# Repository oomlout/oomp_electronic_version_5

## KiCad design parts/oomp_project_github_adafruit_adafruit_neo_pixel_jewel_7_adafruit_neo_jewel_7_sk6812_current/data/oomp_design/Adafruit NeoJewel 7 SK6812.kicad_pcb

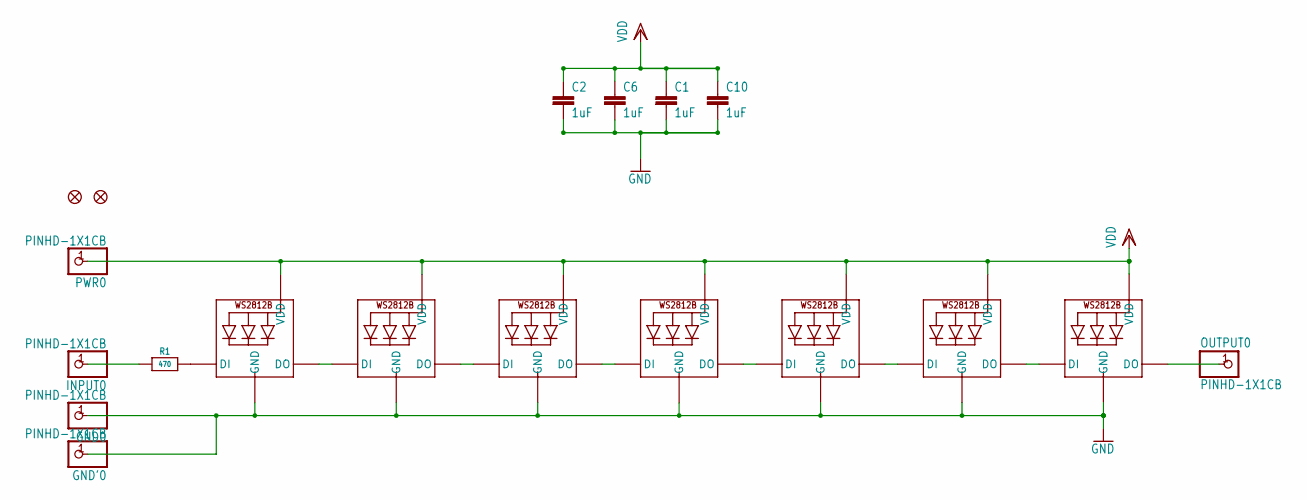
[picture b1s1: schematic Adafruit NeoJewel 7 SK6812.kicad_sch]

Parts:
C1, C2, C6, C10: 1uF; C0603
FID1, FID2: FIDUCIAL_1MM
GND0: PINHD-1X1CB; 1X01-CLEANBIG
GND'0: PINHD-1X1CB; 1X01-CLEANBIG
INPUT0: PINHD-1X1CB; 1X01-CLEANBIG
LED1, LED2, LED3, LED4, LED5, LED6, LED7: WS2812B_5050N; WS2812B-NARROW
OUTPUT0: PINHD-1X1CB; 1X01-CLEANBIG
PWR0: PINHD-1X1CB; 1X01-CLEANBIG
R1: 470; 0603-NO

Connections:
GND: C1.2, C2.2, C6.2, C10.2, GND0.1, GND'0.1, LED1.3-GND (GND), LED2.3-GND (GND), LED3.3-GND (GND), LED4.3-GND (GND), LED5.3-GND (GND), LED6.3-GND (GND), LED7.3-GND (GND)
unnamed: LED1.2-DOUT (DO), LED2.4-DIN (DI)
unnamed: LED2.2-DOUT (DO), LED3.4-DIN (DI)
unnamed: LED3.2-DOUT (DO), LED4.4-DIN (DI)
unnamed: LED4.2-DOUT (DO), LED5.4-DIN (DI)
unnamed: LED5.2-DOUT (DO), LED6.4-DIN (DI)
unnamed: LED6.2-DOUT (DO), LED7.4-DIN (DI)
unnamed: LED7.2-DOUT (DO), OUTPUT0.1
unnamed: LED1.4-DIN (DI), R1.2
unnamed: INPUT0.1, R1.1
VDD: C1.1, C2.1, C6.1, C10.1, LED1.1-VDD (VDD), LED2.1-VDD (VDD), LED3.1-VDD (VDD), LED4.1-VDD (VDD), LED5.1-VDD (VDD), LED6.1-VDD (VDD), LED7.1-VDD (VDD), PWR0.1

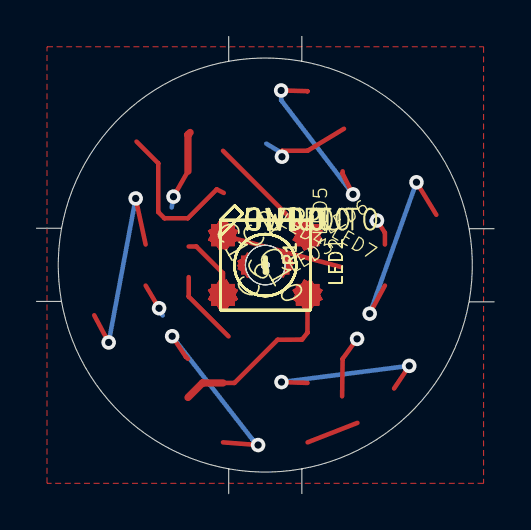
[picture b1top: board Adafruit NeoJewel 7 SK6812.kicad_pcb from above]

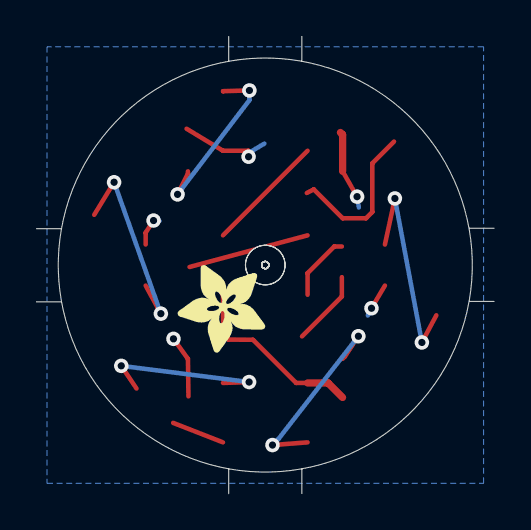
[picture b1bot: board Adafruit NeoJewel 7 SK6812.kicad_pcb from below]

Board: 2 copper layers, 23.0 x 23.0 mm, 52 parts (7 on the bottom side), 11 nets.

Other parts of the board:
PLABEL0: PLABEL0
PLABEL1: PLABEL1
PLABEL2: PLABEL2
PLABEL3: PLABEL3
PLABEL4: PLABEL4
PLABEL5: PLABEL5
PLABEL6: PLABEL6
PLABEL7: PLABEL7
PLABEL8: PLABEL8
PLABEL9: PLABEL9
U$3: ADAFRUIT_5MM
UNK_HOLE_0: dummyfp0
UNK_HOLE_1: dummyfp1
UNK_HOLE_2: dummyfp2
UNK_HOLE_3: dummyfp3
UNK_HOLE_4: dummyfp4
UNK_HOLE_5: dummyfp5
UNK_HOLE_6: dummyfp6
UNK_HOLE_7: dummyfp7
UNK_HOLE_8: dummyfp8
UNK_HOLE_9: dummyfp9
UNK_HOLE_10: dummyfp10
UNK_HOLE_11: dummyfp11
UNK_HOLE_12: dummyfp12
UNK_HOLE_13: dummyfp13
UNK_HOLE_14: dummyfp14
UNK_HOLE_15: dummyfp15
UNK_HOLE_16: dummyfp16
UNK_HOLE_17: dummyfp17
UNK_HOLE_18: dummyfp18
UNK_HOLE_19: dummyfp19
UNK_HOLE_20: dummyfp20
UNK_HOLE_21: dummyfp21

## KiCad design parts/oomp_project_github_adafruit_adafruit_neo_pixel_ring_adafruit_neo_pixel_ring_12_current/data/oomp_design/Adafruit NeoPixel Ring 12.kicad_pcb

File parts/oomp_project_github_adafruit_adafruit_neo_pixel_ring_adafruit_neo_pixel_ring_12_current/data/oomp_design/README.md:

# OOMP KiCad design copy

Open `Adafruit NeoPixel Ring 12.kicad_pro` (or the `.kicad_pcb` / `.kicad_sch`) in KiCad. Local OOMP libraries are under `libraries/`. Original inputs are preserved in [../original/](../original/).

Only verified unchanged installed KiCad defaults were renamed. Modified, custom, unmatched and unavailable items remain unchanged. Soldering variants are never swapped during conversion. Existing pad coordinates, nets and UUIDs are preserved.

See [conversion_report.yaml](conversion_report.yaml) for every conversion and skip. Copy this directory before editing; regeneration refuses to overwrite edited design files.

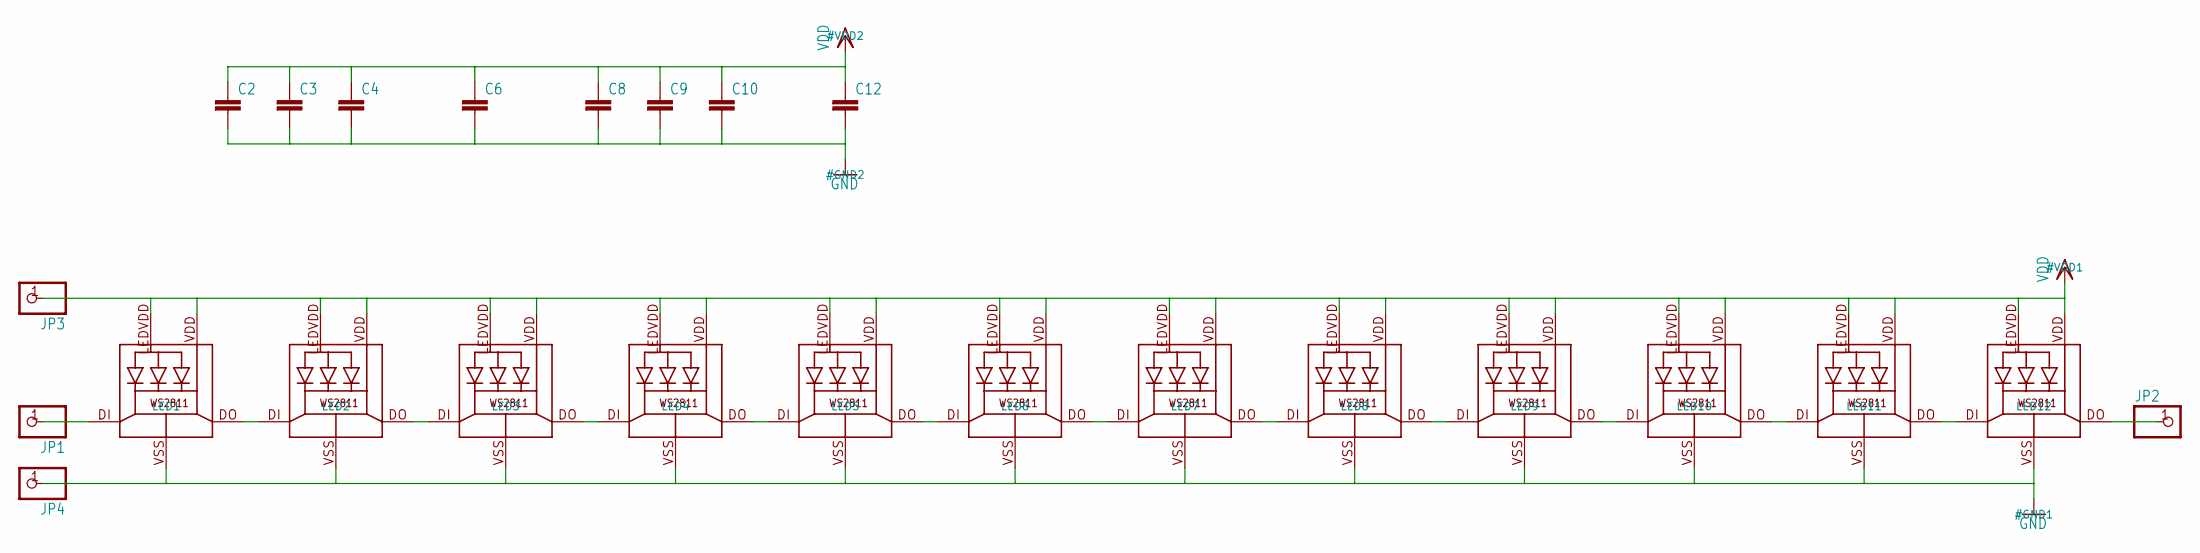
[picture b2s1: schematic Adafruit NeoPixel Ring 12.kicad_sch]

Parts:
C2, C3, C4, C6, C8, C9, C10, C12: C-EUC0603; C0603
JP1, JP2, JP3, JP4: PINHD-1X1CB; 1X01-CLEANBIG
LED1, LED2, LED3, LED4, LED5, LED6, LED7, LED8, LED9, LED10, LED11, LED12: WS28115050

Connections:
GND: C2.2, C3.2, C4.2, C6.2, C8.2, C9.2, C10.2, C12.2, JP4.1, LED1.VSS (GND), LED2.VSS (GND), LED3.VSS (GND), LED4.VSS (GND), LED5.VSS (GND), LED6.VSS (GND), LED7.VSS (GND), LED8.VSS (GND), LED9.VSS (GND), LED10.VSS (GND), LED11.VSS (GND), LED12.VSS (GND)
unnamed: LED1.DO, LED2.DI
unnamed: LED2.DO, LED3.DI
unnamed: LED3.DO, LED4.DI
unnamed: LED4.DO, LED5.DI
unnamed: LED5.DO, LED6.DI
unnamed: LED6.DO, LED7.DI
unnamed: LED7.DO, LED8.DI
unnamed: LED8.DO, LED9.DI
unnamed: LED9.DO, LED10.DI
unnamed: LED10.DO, LED11.DI
unnamed: LED11.DO, LED12.DI
unnamed: JP1.1, LED1.DI
unnamed: JP2.1, LED12.DO
VDD: C2.1, C3.1, C4.1, C6.1, C8.1, C9.1, C10.1, C12.1, JP3.1, LED1.LEDVDD, LED1.VDD, LED2.LEDVDD, LED2.VDD, LED3.LEDVDD, LED3.VDD, LED4.LEDVDD, LED4.VDD, LED5.LEDVDD, LED5.VDD, LED6.LEDVDD, LED6.VDD, LED7.LEDVDD, LED7.VDD, LED8.LEDVDD, LED8.VDD, LED9.LEDVDD, LED9.VDD, LED10.LEDVDD, LED10.VDD, LED11.LEDVDD, LED11.VDD, LED12.LEDVDD, LED12.VDD

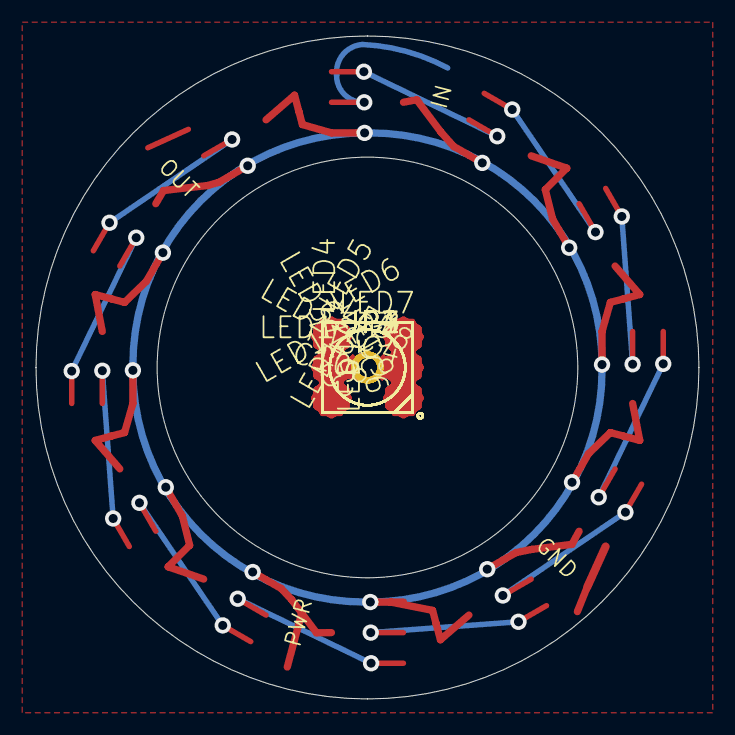
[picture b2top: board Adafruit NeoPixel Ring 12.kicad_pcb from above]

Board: 2 copper layers, 36.8 x 36.8 mm, 27 parts (1 on the bottom side), 15 nets.

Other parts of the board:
U$1, U$2: GUIDE-STAR-12
U$3: ADAFRUIT_5MM

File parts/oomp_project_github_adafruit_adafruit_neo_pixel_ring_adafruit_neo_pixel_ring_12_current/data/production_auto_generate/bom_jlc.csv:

Comment,Designator,Footprint,LCSC Part #
,"JP1,JP2,JP3,JP4",Adafruit NeoPixel Ring 12-import-fps:1X01-CLEANBIG,C7501259
,U$3,Adafruit NeoPixel Ring 12-import-fps:ADAFRUIT_5MM,
,"C2,C3,C4,C6,C8,C9,C10,C12",Adafruit NeoPixel Ring 12-import-fps:C0603,
,"U$1,U$2",Adafruit NeoPixel Ring 12-import-fps:GUIDE-STAR-12,
WS28115050,"LED1,LED2,LED3,LED4,LED5,LED6,LED7,LED8,LED9,LED10,LED11,LED12",Adafruit NeoPixel Ring 12-import-fps:WS28115050,

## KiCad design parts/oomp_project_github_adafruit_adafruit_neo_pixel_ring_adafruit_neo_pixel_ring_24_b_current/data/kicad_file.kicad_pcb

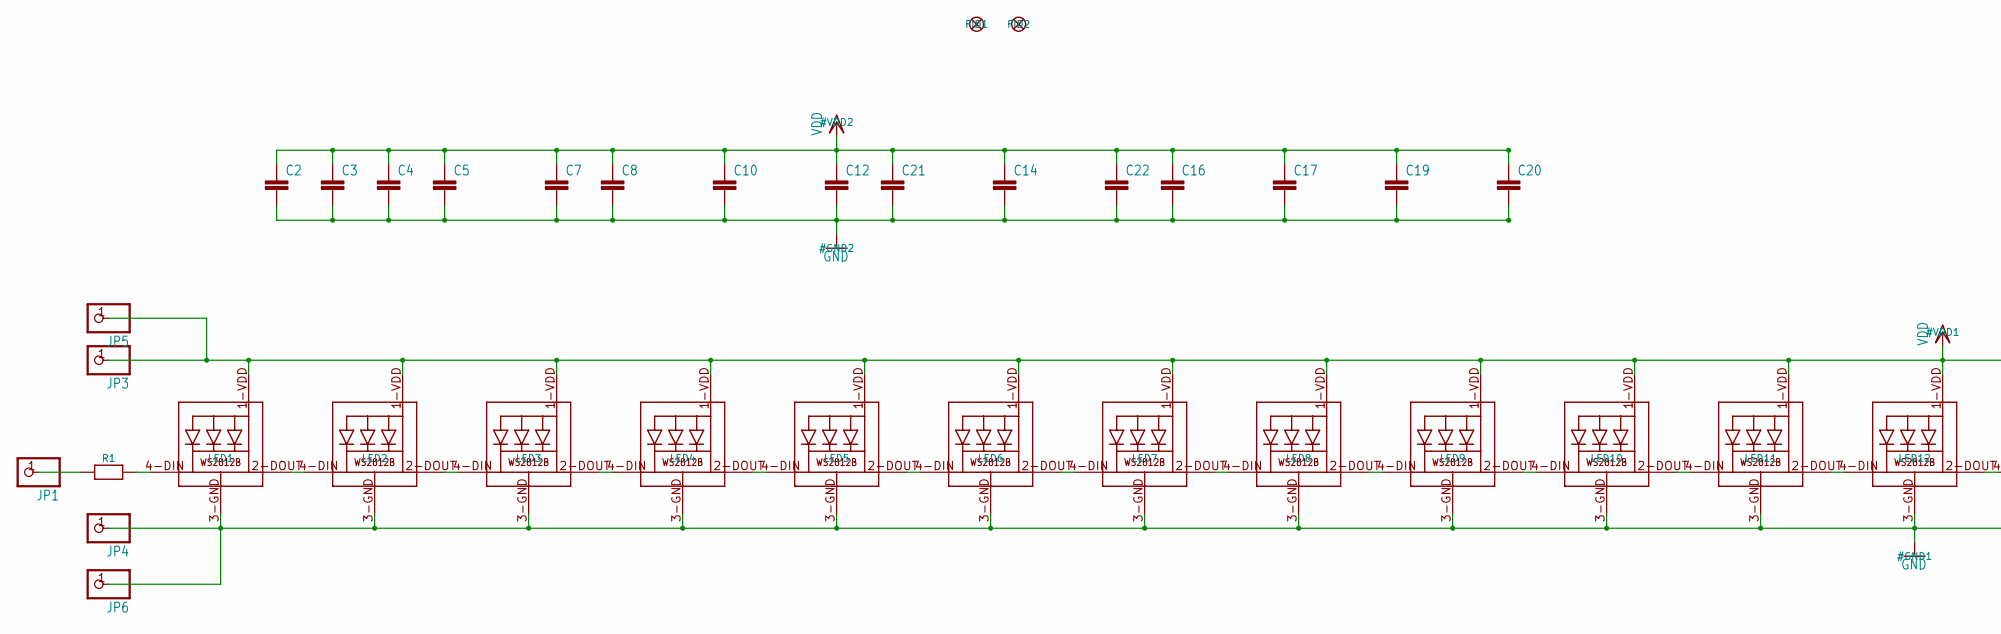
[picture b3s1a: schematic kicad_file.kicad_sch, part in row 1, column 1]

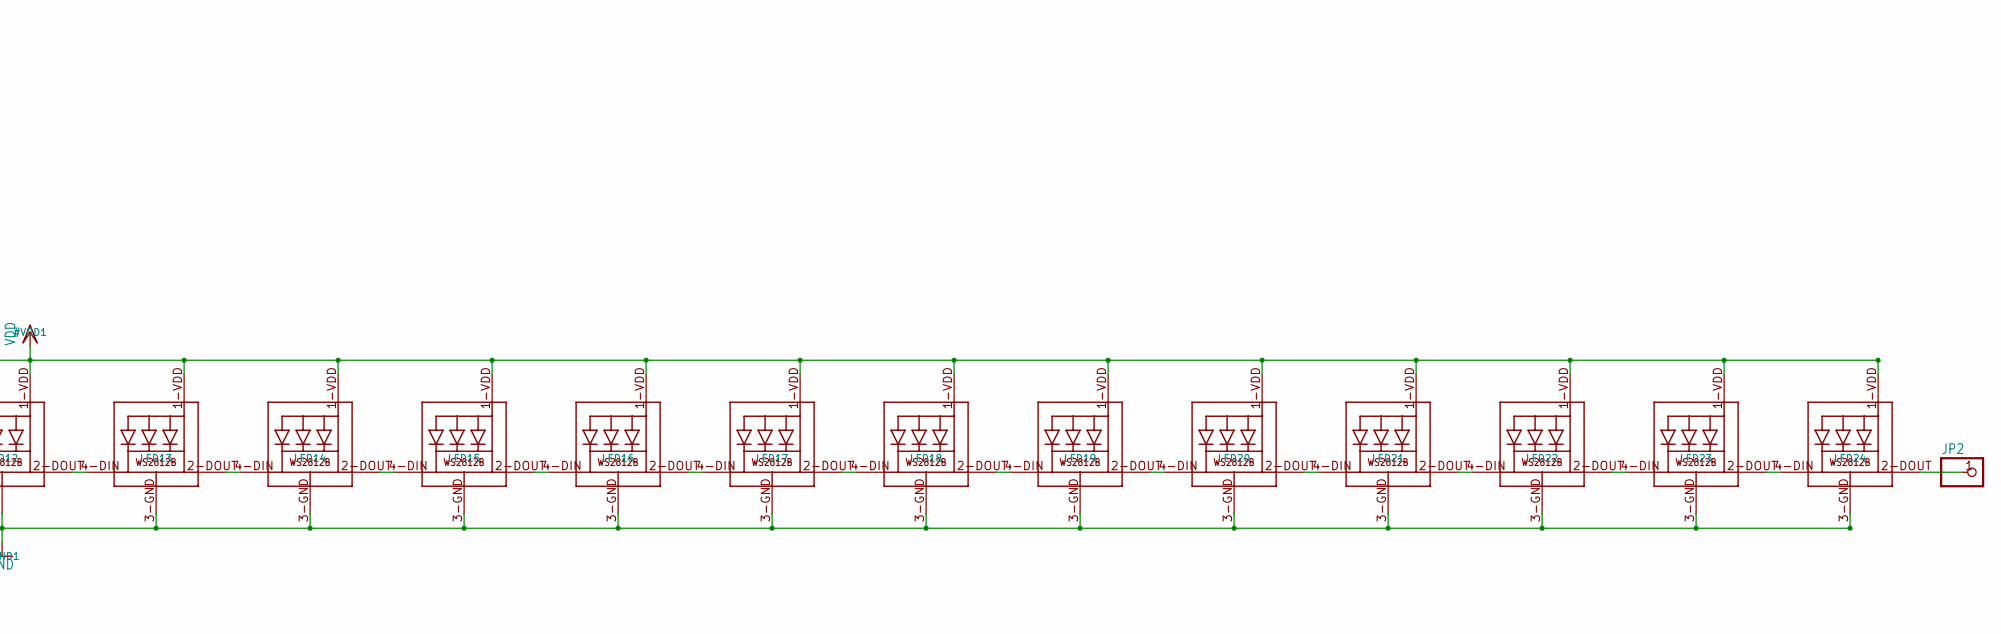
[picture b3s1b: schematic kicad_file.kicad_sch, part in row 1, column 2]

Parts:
C2, C3, C4, C5, C7, C8, C10, C12, C14, C16, C17, C19, C20, C21, C22: C-EUC0603; C0603
FID1, FID2: FIDUCIAL""; FIDUCIAL_1MM
JP1, JP2, JP3, JP4, JP5, JP6: PINHD-1X1CB; 1X01-CLEANBIG
LED1, LED2, LED3, LED4, LED5, LED6, LED7, LED8, LED9, LED10, LED11, LED12, LED13, LED14, LED15, LED16, LED17, LED18, LED19, LED20, LED21, LED22, LED23, LED24: WS2812B5050; WS2812B
R1: RESISTOR_0603_NOOUT; 0603-NO

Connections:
GND: C2.2, C3.2, C4.2, C5.2, C7.2, C8.2, C10.2, C12.2, C14.2, C16.2, C17.2, C19.2, C20.2, C21.2, C22.2, JP4.1, JP6.1, LED1.3-GND (GND), LED2.3-GND (GND), LED3.3-GND (GND), LED4.3-GND (GND), LED5.3-GND (GND), LED6.3-GND (GND), LED7.3-GND (GND), LED8.3-GND (GND), LED9.3-GND (GND), LED10.3-GND (GND), LED11.3-GND (GND), LED12.3-GND (GND), LED13.3-GND (GND), LED14.3-GND (GND), LED15.3-GND (GND), LED16.3-GND (GND), LED17.3-GND (GND), LED18.3-GND (GND), LED19.3-GND (GND), LED20.3-GND (GND), LED21.3-GND (GND), LED22.3-GND (GND), LED23.3-GND (GND), LED24.3-GND (GND)
unnamed: LED1.2-DOUT (DO), LED2.4-DIN (DI)
unnamed: LED2.2-DOUT (DO), LED3.4-DIN (DI)
unnamed: LED3.2-DOUT (DO), LED4.4-DIN (DI)
unnamed: LED4.2-DOUT (DO), LED5.4-DIN (DI)
unnamed: LED5.2-DOUT (DO), LED6.4-DIN (DI)
unnamed: LED6.2-DOUT (DO), LED7.4-DIN (DI)
unnamed: LED7.2-DOUT (DO), LED8.4-DIN (DI)
unnamed: LED8.2-DOUT (DO), LED9.4-DIN (DI)
unnamed: LED9.2-DOUT (DO), LED10.4-DIN (DI)
unnamed: LED10.2-DOUT (DO), LED11.4-DIN (DI)
unnamed: LED11.2-DOUT (DO), LED12.4-DIN (DI)
unnamed: LED12.2-DOUT (DO), LED13.4-DIN (DI)
unnamed: LED13.2-DOUT (DO), LED14.4-DIN (DI)
unnamed: LED14.2-DOUT (DO), LED15.4-DIN (DI)
unnamed: LED15.2-DOUT (DO), LED16.4-DIN (DI)
unnamed: LED16.2-DOUT (DO), LED17.4-DIN (DI)
unnamed: LED17.2-DOUT (DO), LED18.4-DIN (DI)
unnamed: LED18.2-DOUT (DO), LED19.4-DIN (DI)
unnamed: LED19.2-DOUT (DO), LED20.4-DIN (DI)
unnamed: LED20.2-DOUT (DO), LED21.4-DIN (DI)
unnamed: LED21.2-DOUT (DO), LED22.4-DIN (DI)
unnamed: LED22.2-DOUT (DO), LED23.4-DIN (DI)
unnamed: LED23.2-DOUT (DO), LED24.4-DIN (DI)
unnamed: JP2.1, LED24.2-DOUT (DO)
unnamed: LED1.4-DIN (DI), R1.2
unnamed: JP1.1, R1.1
VDD: C2.1, C3.1, C4.1, C5.1, C7.1, C8.1, C10.1, C12.1, C14.1, C16.1, C17.1, C19.1, C20.1, C21.1, C22.1, JP3.1, JP5.1, LED1.1-VDD (VDD), LED2.1-VDD (VDD), LED3.1-VDD (VDD), LED4.1-VDD (VDD), LED5.1-VDD (VDD), LED6.1-VDD (VDD), LED7.1-VDD (VDD), LED8.1-VDD (VDD), LED9.1-VDD (VDD), LED10.1-VDD (VDD), LED11.1-VDD (VDD), LED12.1-VDD (VDD), LED13.1-VDD (VDD), LED14.1-VDD (VDD), LED15.1-VDD (VDD), LED16.1-VDD (VDD), LED17.1-VDD (VDD), LED18.1-VDD (VDD), LED19.1-VDD (VDD), LED20.1-VDD (VDD), LED21.1-VDD (VDD), LED22.1-VDD (VDD), LED23.1-VDD (VDD), LED24.1-VDD (VDD)

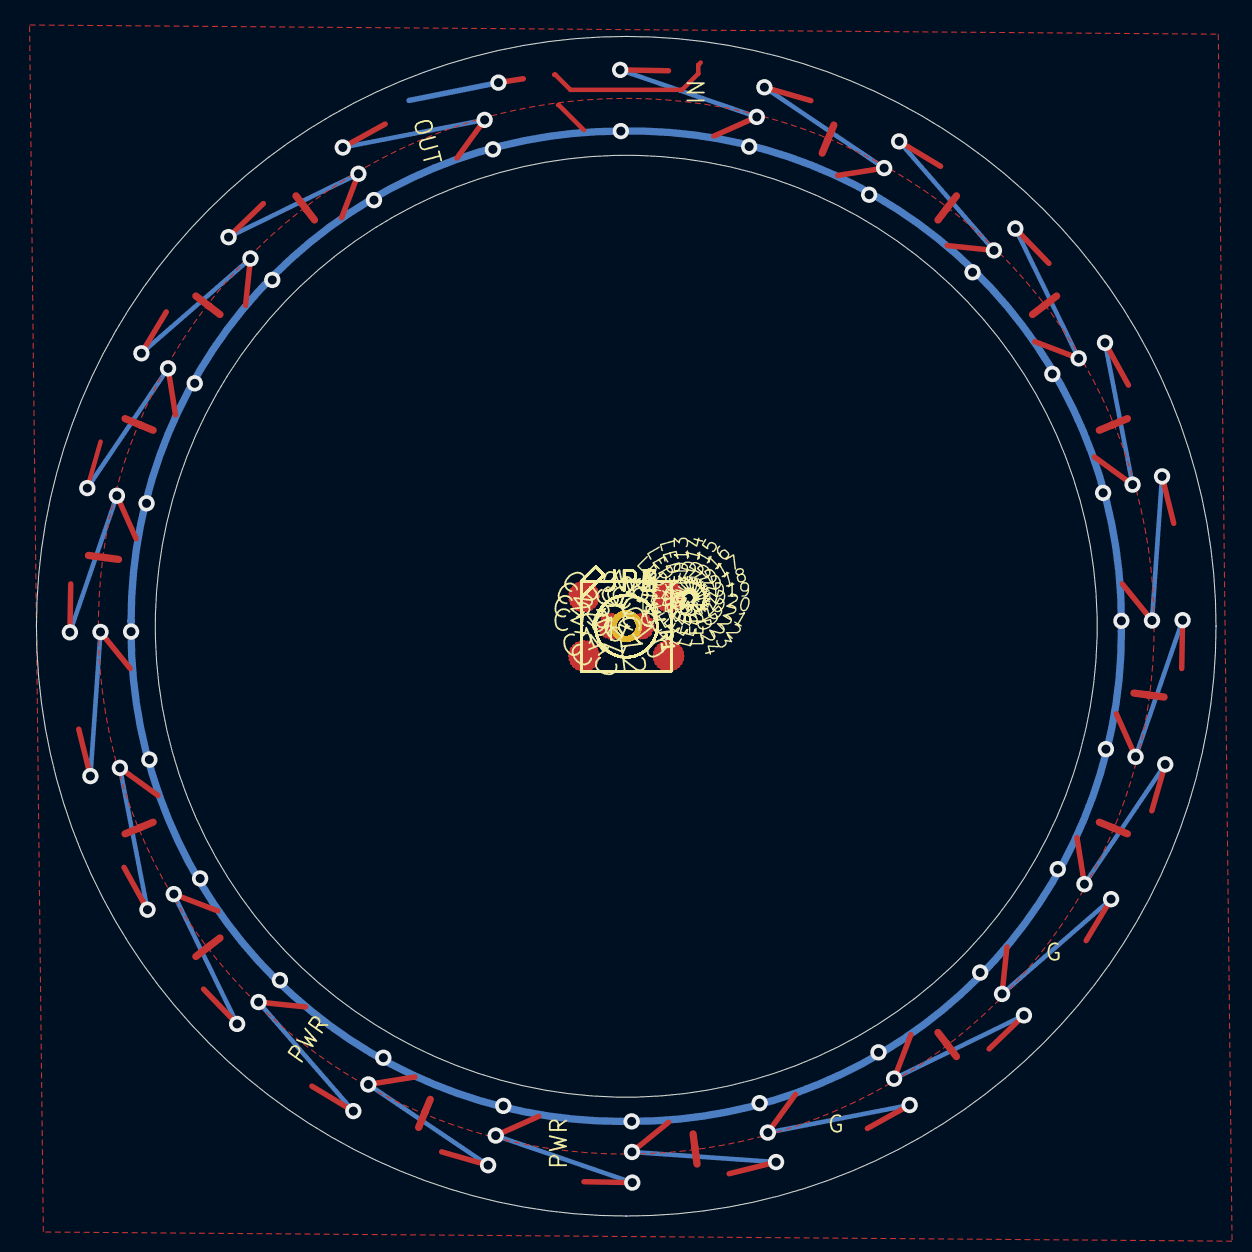
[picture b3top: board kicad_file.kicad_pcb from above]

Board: 2 copper layers, 65.5 x 65.5 mm, 49 parts (1 on the bottom side), 28 nets.

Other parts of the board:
U$1: ADAFRUIT_5MM

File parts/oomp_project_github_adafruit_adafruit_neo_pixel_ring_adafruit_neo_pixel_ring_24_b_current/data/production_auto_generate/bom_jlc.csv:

Comment,Designator,Footprint,LCSC Part #
,R1,Adafruit NeoPixel Ring 24 B-import-fps:0603-NO,
,"JP1,JP2,JP3,JP4,JP5,JP6",Adafruit NeoPixel Ring 24 B-import-fps:1X01-CLEANBIG,C7501259
,U$1,Adafruit NeoPixel Ring 24 B-import-fps:ADAFRUIT_5MM,
,"C2,C3,C4,C5,C7,C8,C10,C12,C14,C16,C17,C19,C20,C21,C22",Adafruit NeoPixel Ring 24 B-import-fps:C0603,
WS2812B5050,"LED1,LED2,LED3,LED4,LED5,LED6,LED7,LED8,LED9,LED10,LED11,LED12,LED13,LED14,LED15,LED16,LED17,LED18,LED19,LED20,LED21,LED22,LED23,LED24",Adafruit NeoPixel Ring 24 B-import-fps:WS2812B-NARROW,
